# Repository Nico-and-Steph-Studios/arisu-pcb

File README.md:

# In Progress

# Arisu Keyboard PCB
アリス PCB designed using KiCad. The layout is inspired by Lyn's EM7 and TGR Alice with some modification of my own.

Key differences:
- I removed the extra [B] key on the right half and shifted the [NM,.?] row to the left by 0.25U.
- Shifted the 3 keys to the right and added arrow keys.
- Tweaked the bottom so that the 1.5U keys doesn't protrude out a little.

Shifting the [NM,.?] row to the left by 0.25U required quite some work on the arrangement of keys for the right half.
As a result, this does not give the same typing experience as Lyn's EM7 and TGR Alice.
Lyn's EM7 and TGR Alice uses the home row as the center point to vertically align both halves while I used the number row instead.
Due to the nature of staggered keyboards, aligning using the number row resulted in the home row not being aligned.

Disclaimer: Use these files at your own risk.

## Gerber Files
Download the gerber files under [releases](https://github.com/FateNozomi/arisu-pcb/releases).

## Assembly
For the components required, you may refer to the bill of materials included along with the release as reference or load up the design file in KiCad.
All the components can be soldered using a regular soldering iron, though soldering the Micro USB receptacle might be the biggest hurdle.

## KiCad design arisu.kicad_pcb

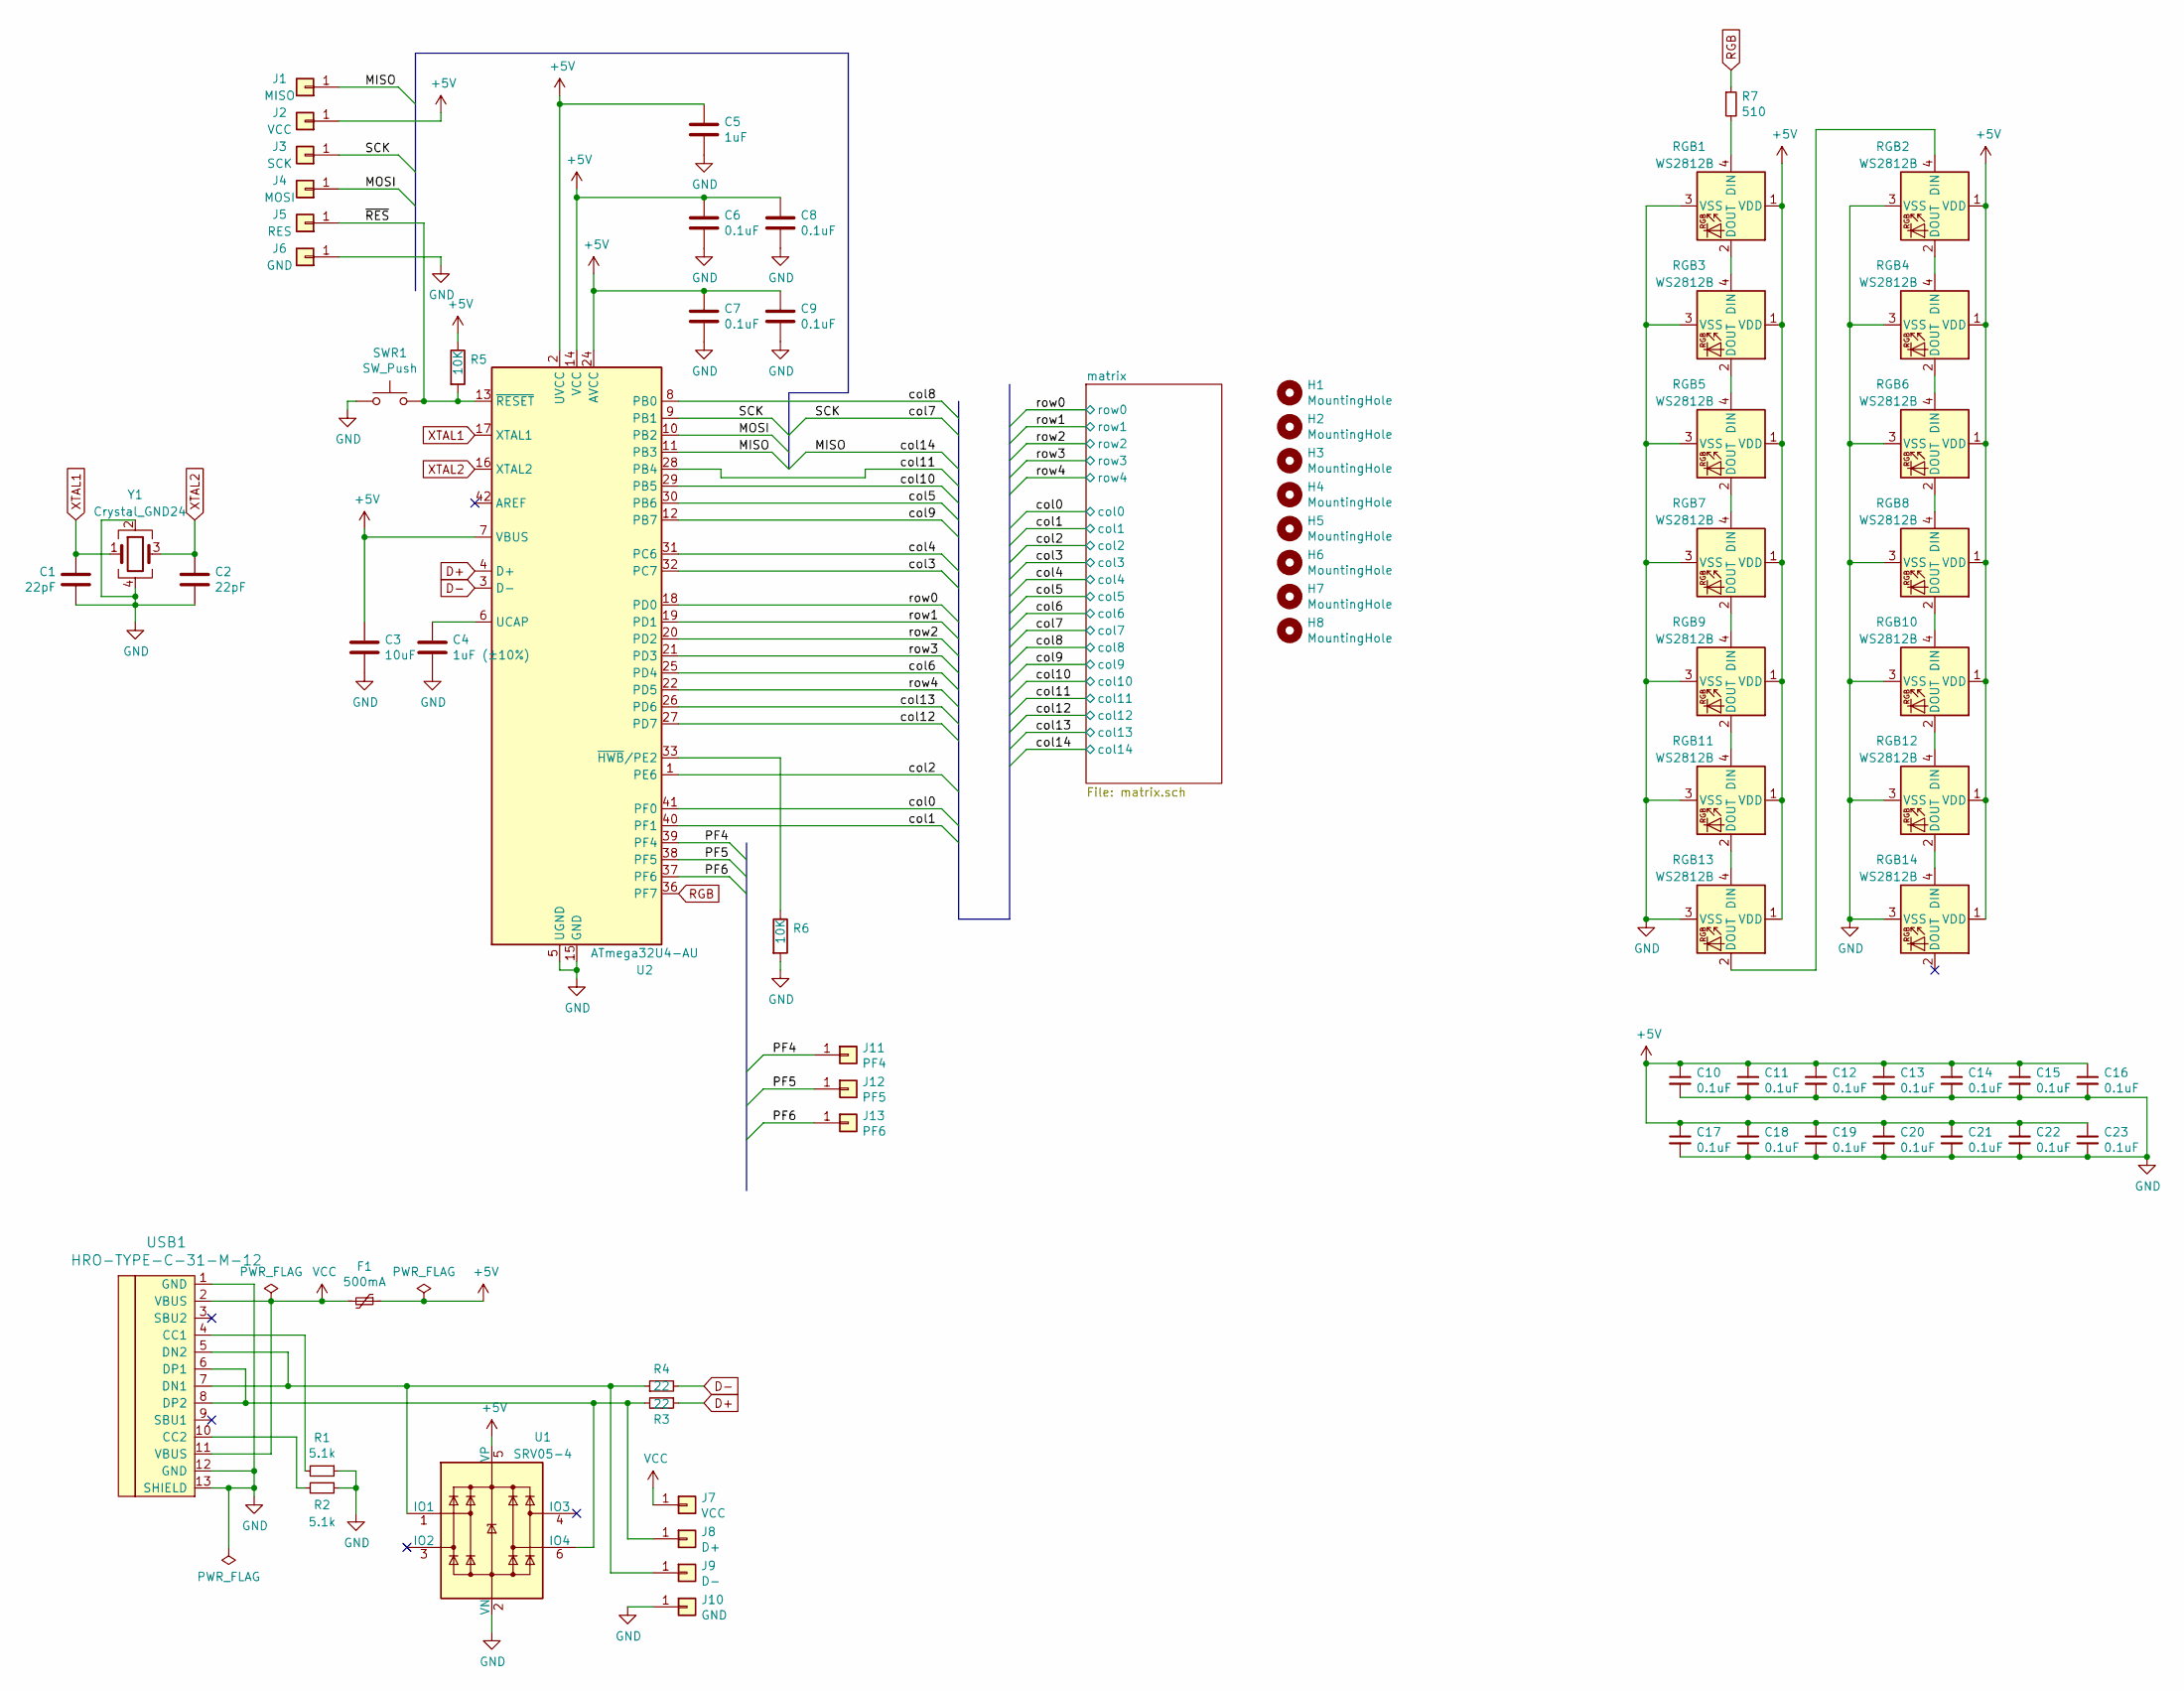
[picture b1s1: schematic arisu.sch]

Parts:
C1, C2: 22pF; C_0805_2012Metric_Pad1.18x1.45mm_HandSolder
C3: 10uF; C_0805_2012Metric_Pad1.18x1.45mm_HandSolder
C4: 1uF (±10%); C_0805_2012Metric_Pad1.18x1.45mm_HandSolder
C5: 1uF; C_0805_2012Metric_Pad1.18x1.45mm_HandSolder
C6, C7, C8, C9, C10, C11, C12, C13, C14, C15, C16, C17, C18, C19, C20, C21, C22, C23: 0.1uF; C_0805_2012Metric_Pad1.18x1.45mm_HandSolder
F1: 500mA; Fuse_1206_3216Metric_Pad1.42x1.75mm_HandSolder
H1, H2, H3, H4, H5, H6, H7, H8: MountingHole; MountingHole_2.2mm_M2_Pad
J1: MISO; PinHeader_1x01_P2.54mm_Vertical
J2, J7: VCC; PinHeader_1x01_P2.54mm_Vertical
J3: SCK; PinHeader_1x01_P2.54mm_Vertical
J4: MOSI; PinHeader_1x01_P2.54mm_Vertical
J5: RES; PinHeader_1x01_P2.54mm_Vertical
J6, J10: GND; PinHeader_1x01_P2.54mm_Vertical
J8: D+; PinHeader_1x01_P2.54mm_Vertical
J9: D-; PinHeader_1x01_P2.54mm_Vertical
J11: PF4; PinHeader_1x01_P2.54mm_Vertical
J12: PF5; PinHeader_1x01_P2.54mm_Vertical
J13: PF6; PinHeader_1x01_P2.54mm_Vertical
R1, R2: 5.1k; R_0805_2012Metric_Pad1.20x1.40mm_HandSolder
R3, R4: 22; R_0805_2012Metric_Pad1.20x1.40mm_HandSolder
R5, R6: 10K; R_0805_2012Metric_Pad1.20x1.40mm_HandSolder
R7: 510; R_0805_2012Metric_Pad1.20x1.40mm_HandSolder
RGB1, RGB2, RGB3, RGB4, RGB5, RGB6, RGB7, RGB8, RGB9, RGB10, RGB11, RGB12, RGB13, RGB14: WS2812B; LED_WS2812B_PLCC4_5.0x5.0mm_P3.2mm
SWR1: SW_Push; SW_SPST_TL3342
U1: SRV05-4; SOT-23-6
U2: ATmega32U4-AU; TQFP-44_10x10mm_Pitch0.8mm
USB1: HRO-TYPE-C-31-M-12; HRO-TYPE-C-31-M-12-HandSoldering
Y1: Crystal_GND24; Crystal_SMD_SeikoEpson_FA238-4pin_3.2x2.5mm_HandSoldering

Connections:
+5V: C3.1, C5.1, C6.1, C7.1, C8.1, C9.1, C10.1, C11.1, C12.1, C13.1, C14.1, C15.1, C16.1, C17.1, C18.1, C19.1, C20.1, C21.1, C22.1, C23.1, F1.1, J2.1, R5.1, RGB1.1 (VDD), RGB2.1 (VDD), RGB3.1 (VDD), RGB4.1 (VDD), RGB5.1 (VDD), RGB6.1 (VDD), RGB7.1 (VDD), RGB8.1 (VDD), RGB9.1 (VDD), RGB10.1 (VDD), RGB11.1 (VDD), RGB12.1 (VDD), RGB13.1 (VDD), RGB14.1 (VDD), U1.5 (VP), U2.2 (UVCC), U2.7 (VBUS), U2.14 (VCC), U2.24 (AVCC), U2.34 (VCC), U2.44 (AVCC)
/MISO: J1.1, U2.11 (PB3); also elsewhere on the board
/MOSI: J4.1, U2.10 (PB2)
/PF4: J11.1, U2.39 (PF4)
/PF5: J12.1, U2.38 (PF5)
/PF6: J13.1, U2.37 (PF6)
/SCK: J3.1, U2.9 (PB1); also elsewhere on the board
/col0: U2.41 (PF0); also elsewhere on the board
/col1: U2.40 (PF1); also elsewhere on the board
/col2: U2.1 (PE6); also elsewhere on the board
/col3: U2.32 (PC7); also elsewhere on the board
/col4: U2.31 (PC6); also elsewhere on the board
/col5: U2.30 (PB6); also elsewhere on the board
/col6: U2.25 (PD4); also elsewhere on the board
/col8: U2.8 (PB0); also elsewhere on the board
/col9: U2.12 (PB7); also elsewhere on the board
/col10: U2.29 (PB5); also elsewhere on the board
/col11: U2.28 (PB4); also elsewhere on the board
/col12: U2.27 (PD7); also elsewhere on the board
/col13: U2.26 (PD6); also elsewhere on the board
/row0: U2.18 (PD0); also elsewhere on the board
/row1: U2.19 (PD1); also elsewhere on the board
/row2: U2.20 (PD2); also elsewhere on the board
/row3: U2.21 (PD3); also elsewhere on the board
/row4: U2.22 (PD5); also elsewhere on the board
/~RES~: J5.1, R5.2, SWR1.2, U2.13 (~RESET)
D+: R4.1, U2.4 (D+)
D-: R3.2, U2.3 (D-)
GND: C1.1, C2.2, C3.2, C4.2, C5.2, C6.2, C7.2, C8.2, C9.2, C10.2, C11.2, C12.2, C13.2, C14.2, C15.2, C16.2, C17.2, C18.2, C19.2, C20.2, C21.2, C22.2, C23.2, J6.1, J10.1, R1.1, R2.1, R6.2, RGB1.3 (VSS), RGB2.3 (VSS), RGB3.3 (VSS), RGB4.3 (VSS), RGB5.3 (VSS), RGB6.3 (VSS), RGB7.3 (VSS), RGB8.3 (VSS), RGB9.3 (VSS), RGB10.3 (VSS), RGB11.3 (VSS), RGB12.3 (VSS), RGB13.3 (VSS), RGB14.3 (VSS), SWR1.1, U1.2 (VN), U2.5 (UGND), U2.15 (GND), U2.23 (GND), U2.35 (GND), U2.43 (GND), USB1.1 (GND), USB1.12 (GND), USB1.13 (SHIELD), Y1.2, Y1.4
unnamed: C4.1, U2.6 (UCAP)
unnamed: J8.1, R4.2, U1.6 (IO4), USB1.6 (DP1), USB1.8 (DP2)
unnamed: J9.1, R3.1, U1.1 (IO1), USB1.5 (DN2), USB1.7 (DN1)
unnamed: R1.2, USB1.4 (CC1)
unnamed: R2.2, USB1.10 (CC2)
unnamed: R6.1, U2.33 (~HWB~/PE2)
unnamed: R7.2, RGB1.4 (DIN)
unnamed: RGB1.2 (DOUT), RGB3.4 (DIN)
unnamed: RGB2.2 (DOUT), RGB4.4 (DIN)
unnamed: RGB3.2 (DOUT), RGB5.4 (DIN)
unnamed: RGB4.2 (DOUT), RGB6.4 (DIN)
unnamed: RGB5.2 (DOUT), RGB7.4 (DIN)
unnamed: RGB6.2 (DOUT), RGB8.4 (DIN)
unnamed: RGB7.2 (DOUT), RGB9.4 (DIN)
unnamed: RGB10.2 (DOUT), RGB12.4 (DIN)
unnamed: RGB8.2 (DOUT), RGB10.4 (DIN)
unnamed: RGB11.2 (DOUT), RGB13.4 (DIN)
unnamed: RGB9.2 (DOUT), RGB11.4 (DIN)
unnamed: RGB12.2 (DOUT), RGB14.4 (DIN)
unnamed: RGB2.4 (DIN), RGB13.2 (DOUT)
RGB: R7.1, U2.36 (PF7)
VCC: F1.2, J7.1, USB1.2 (VBUS), USB1.11 (VBUS)
XTAL1: C1.2, U2.17 (XTAL1), Y1.1
XTAL2: C2.1, U2.16 (XTAL2), Y1.3

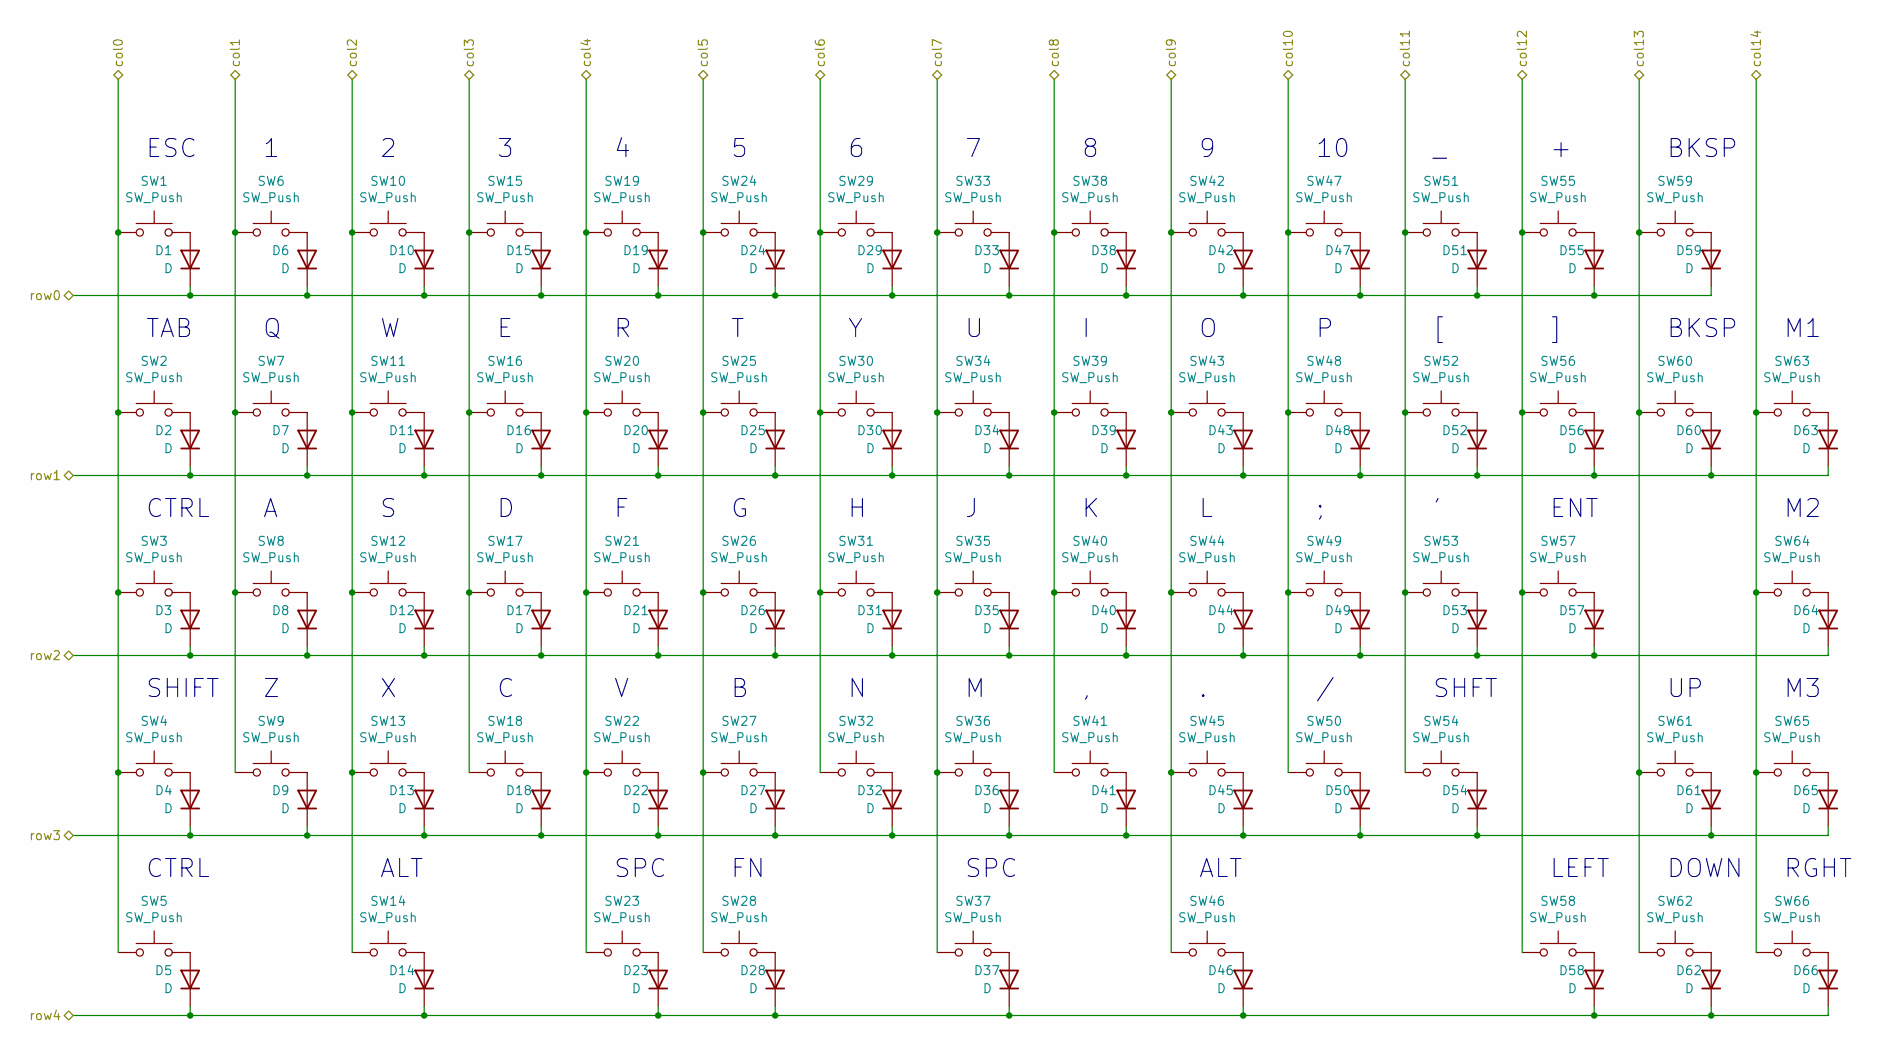
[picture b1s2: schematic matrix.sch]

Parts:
D1, D2, D3, D4, D5, D6, D7, D8, D9, D10, D11, D12, D13, D14, D15, D16, D17, D18, D19, D20, D21, D22, D23, D24, D25, D26, D27, D28, D29, D30, D31, D32, D33, D34, D35, D36, D37, D38, D39, D40, D41, D42, D43, D44, D45, D46, D47, D48, D49, D50, D51, D52, D53, D54, D55, D56, D57, D58, D59, D60, D61, D62, D63, D64, D65, D66: D; D_SOD-123
SW1, SW6, SW7, SW8, SW9, SW10, SW11, SW12, SW13, SW15, SW16, SW17, SW18, SW19, SW20, SW21, SW22, SW24, SW25, SW26, SW27, SW28, SW29, SW30, SW31, SW32, SW33, SW34, SW35, SW36, SW38, SW39, SW40, SW41, SW42, SW43, SW44, SW45, SW47, SW48, SW49, SW50, SW51, SW52, SW53, SW55, SW56, SW58, SW61, SW62, SW63, SW64, SW65, SW66: SW_Push; MXOnly-1U-Hotswap
SW2, SW5, SW46, SW60: SW_Push; MXOnly-1.5U-Hotswap
SW3, SW54: SW_Push; MXOnly-1.75U-Hotswap
SW4: SW_Push; MXOnly-2.25U-Hotswap
SW14: SW_Push; MXOnly-1.25U-Hotswap
SW23, SW57: SW_Push; MXOnly-2.25U-Hotswap-ReversedStabilizers
SW37: SW_Push; MXOnly-2.75U-Hotswap-ReversedStabilizers
SW59: SW_Push; MXOnly-2U-Hotswap

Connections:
/MISO: SW63.1, SW64.1, SW65.1, SW66.1; also elsewhere on the board
/SCK: SW33.1, SW34.1, SW35.1, SW36.1, SW37.1; also elsewhere on the board
/col0: SW1.1, SW2.1, SW3.1, SW4.1, SW5.1; also elsewhere on the board
/col1: SW6.1, SW7.1, SW8.1, SW9.1; also elsewhere on the board
/col2: SW10.1, SW11.1, SW12.1, SW13.1, SW14.1; also elsewhere on the board
/col3: SW15.1, SW16.1, SW17.1, SW18.1; also elsewhere on the board
/col4: SW19.1, SW20.1, SW21.1, SW22.1, SW23.1; also elsewhere on the board
/col5: SW24.1, SW25.1, SW26.1, SW27.1, SW28.1; also elsewhere on the board
/col6: SW29.1, SW30.1, SW31.1, SW32.1; also elsewhere on the board
/col8: SW38.1, SW39.1, SW40.1, SW41.1; also elsewhere on the board
/col9: SW42.1, SW43.1, SW44.1, SW45.1, SW46.1; also elsewhere on the board
/col10: SW47.1, SW48.1, SW49.1, SW50.1; also elsewhere on the board
/col11: SW51.1, SW52.1, SW53.1, SW54.1; also elsewhere on the board
/col12: SW55.1, SW56.1, SW57.1, SW58.1; also elsewhere on the board
/col13: SW59.1, SW60.1, SW61.1, SW62.1; also elsewhere on the board
/row0: D1.1 (K), D6.1 (K), D10.1 (K), D15.1 (K), D19.1 (K), D24.1 (K), D29.1 (K), D33.1 (K), D38.1 (K), D42.1 (K), D47.1 (K), D51.1 (K), D55.1 (K), D59.1 (K); also elsewhere on the board
/row1: D2.1 (K), D7.1 (K), D11.1 (K), D16.1 (K), D20.1 (K), D25.1 (K), D30.1 (K), D34.1 (K), D39.1 (K), D43.1 (K), D48.1 (K), D52.1 (K), D56.1 (K), D60.1 (K), D63.1 (K); also elsewhere on the board
/row2: D3.1 (K), D8.1 (K), D12.1 (K), D17.1 (K), D21.1 (K), D26.1 (K), D31.1 (K), D35.1 (K), D40.1 (K), D44.1 (K), D49.1 (K), D53.1 (K), D57.1 (K), D64.1 (K); also elsewhere on the board
/row3: D4.1 (K), D9.1 (K), D13.1 (K), D18.1 (K), D22.1 (K), D27.1 (K), D32.1 (K), D36.1 (K), D41.1 (K), D45.1 (K), D50.1 (K), D54.1 (K), D61.1 (K), D65.1 (K); also elsewhere on the board
/row4: D5.1 (K), D14.1 (K), D23.1 (K), D28.1 (K), D37.1 (K), D46.1 (K), D58.1 (K), D62.1 (K), D66.1 (K); also elsewhere on the board
unnamed: D1.2 (A), SW1.2
unnamed: D2.2 (A), SW2.2
unnamed: D3.2 (A), SW3.2
unnamed: D4.2 (A), SW4.2
unnamed: D5.2 (A), SW5.2
unnamed: D6.2 (A), SW6.2
unnamed: D7.2 (A), SW7.2
unnamed: D8.2 (A), SW8.2
unnamed: D9.2 (A), SW9.2
unnamed: D10.2 (A), SW10.2
unnamed: D11.2 (A), SW11.2
unnamed: D12.2 (A), SW12.2
unnamed: D13.2 (A), SW13.2
unnamed: D14.2 (A), SW14.2
unnamed: D15.2 (A), SW15.2
unnamed: D16.2 (A), SW16.2
unnamed: D17.2 (A), SW17.2
unnamed: D18.2 (A), SW18.2
unnamed: D19.2 (A), SW19.2
unnamed: D20.2 (A), SW20.2
unnamed: D21.2 (A), SW21.2
unnamed: D22.2 (A), SW22.2
unnamed: D23.2 (A), SW23.2
unnamed: D24.2 (A), SW24.2
unnamed: D25.2 (A), SW25.2
unnamed: D26.2 (A), SW26.2
unnamed: D27.2 (A), SW27.2
unnamed: D28.2 (A), SW28.2
unnamed: D29.2 (A), SW29.2
unnamed: D30.2 (A), SW30.2
unnamed: D31.2 (A), SW31.2
unnamed: D32.2 (A), SW32.2
unnamed: D33.2 (A), SW33.2
unnamed: D34.2 (A), SW34.2
unnamed: D35.2 (A), SW35.2
unnamed: D36.2 (A), SW36.2
unnamed: D37.2 (A), SW37.2
unnamed: D38.2 (A), SW38.2
unnamed: D39.2 (A), SW39.2
unnamed: D40.2 (A), SW40.2
unnamed: D41.2 (A), SW41.2
unnamed: D42.2 (A), SW42.2
unnamed: D43.2 (A), SW43.2
unnamed: D44.2 (A), SW44.2
unnamed: D45.2 (A), SW45.2
unnamed: D46.2 (A), SW46.2
unnamed: D47.2 (A), SW47.2
unnamed: D48.2 (A), SW48.2
unnamed: D49.2 (A), SW49.2
unnamed: D50.2 (A), SW50.2
unnamed: D51.2 (A), SW51.2
unnamed: D52.2 (A), SW52.2
unnamed: D53.2 (A), SW53.2
unnamed: D54.2 (A), SW54.2
unnamed: D55.2 (A), SW55.2
unnamed: D56.2 (A), SW56.2
unnamed: D57.2 (A), SW57.2
unnamed: D58.2 (A), SW58.2
unnamed: D59.2 (A), SW59.2
unnamed: D60.2 (A), SW60.2
unnamed: D61.2 (A), SW61.2
unnamed: D62.2 (A), SW62.2
unnamed: D63.2 (A), SW63.2
unnamed: D64.2 (A), SW64.2
unnamed: D65.2 (A), SW65.2
unnamed: D66.2 (A), SW66.2

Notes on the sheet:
ESC
TAB
BKSP
CTRL
ENT
SHIFT
SHFT
ALT
SPC
DOWN
LEFT
RGHT

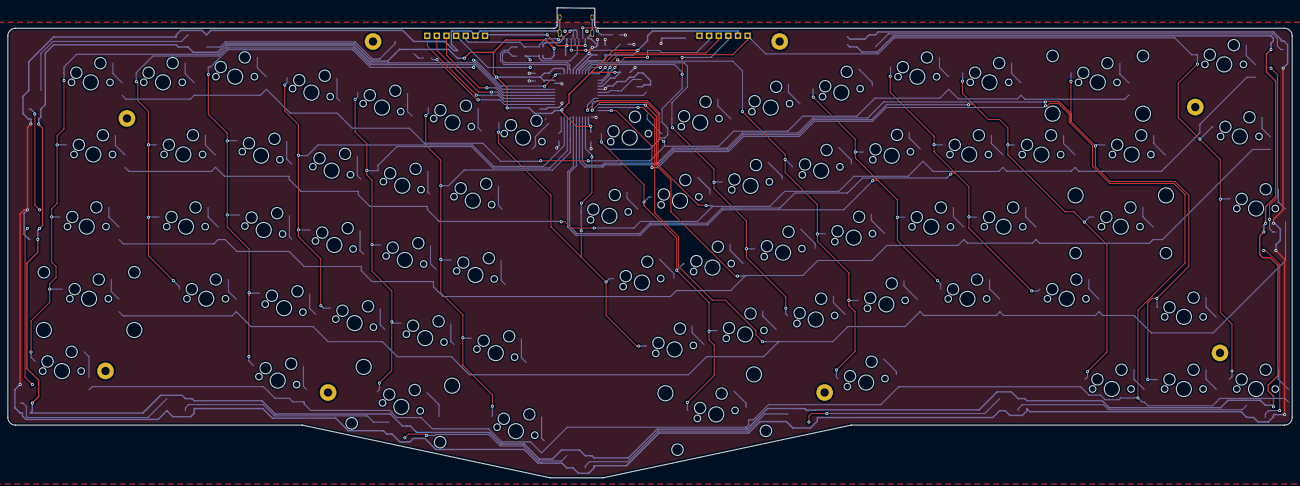
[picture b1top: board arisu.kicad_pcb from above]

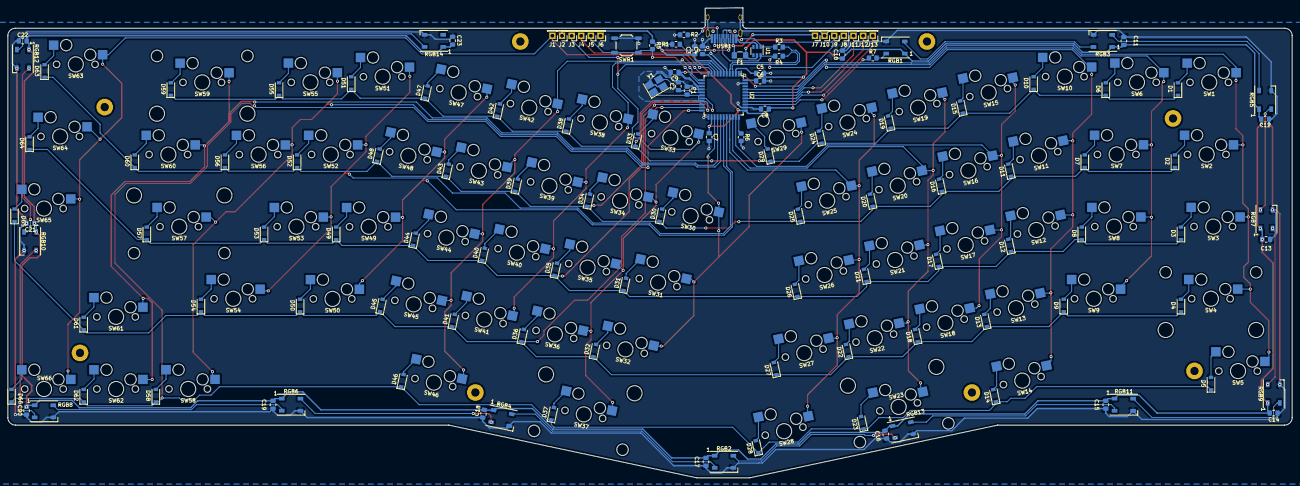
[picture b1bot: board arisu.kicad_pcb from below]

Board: 2 copper layers, 339.1 x 124.1 mm, 203 parts (129 on the bottom side), 119 nets.

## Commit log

2021-03-19 Initial Commit
    Initial Commit
2021-03-22 Add libraries
    Add libraries
2021-03-22 Add hotswap and USB-C
    Add hotswap and USB-C
2021-03-23 Update footprints
    Update backspace to 2U, left spacebar to 2.25U, left Alt to 1.25U
2021-03-23 RGB in Progress
    RGB in Progress
2021-03-24 Add RGB
    Finish RGB
